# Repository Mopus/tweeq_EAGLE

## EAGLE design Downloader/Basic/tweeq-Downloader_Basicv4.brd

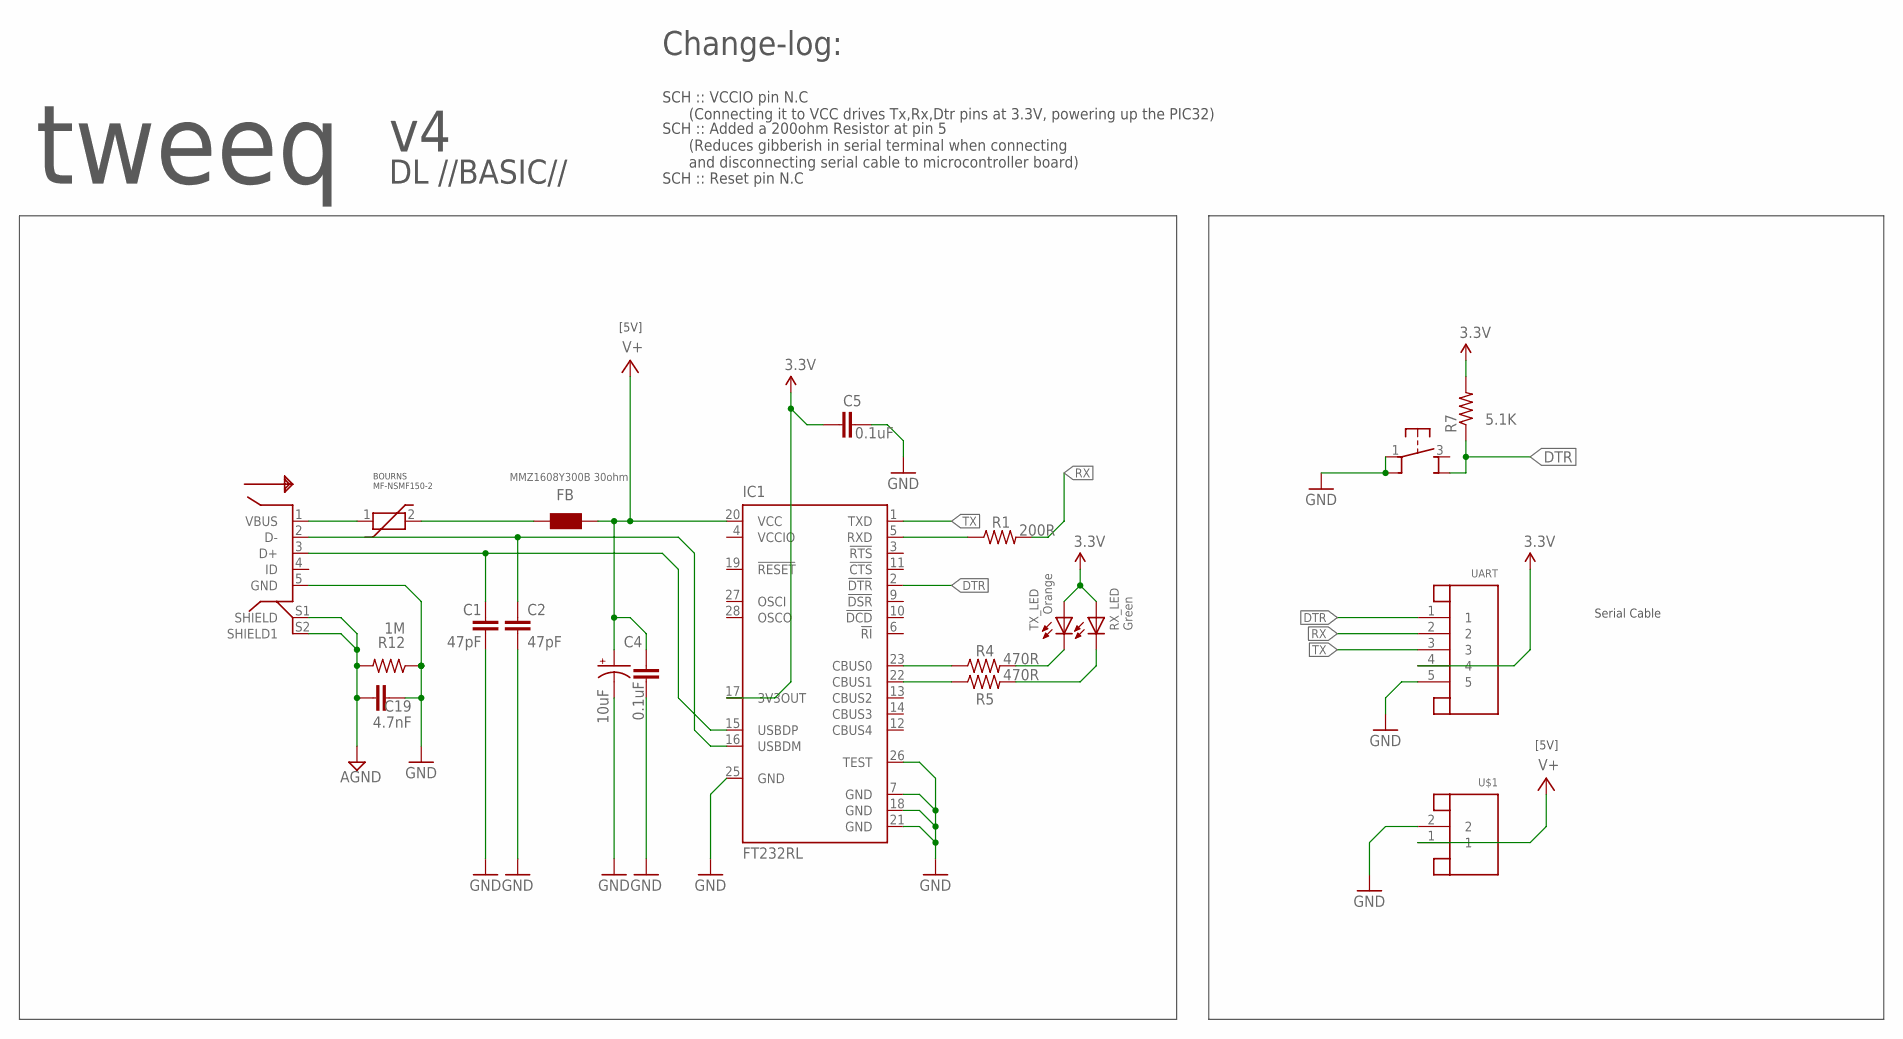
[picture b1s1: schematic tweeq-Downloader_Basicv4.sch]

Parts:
C1, C2: 47pF; C0603K
C3: 10uF; SMC_A
C4, C5: 0.1uF; C0603K
C19: 4.7nF; C0603K
FB: MMZ1608Y300B 30ohm; 0603
IC1: FT232RL; SSOP28
PTC_FUSE: PTC_FUSE/MF-NSMF150-2; 1206F
R1: 200R; R0603
R4, R5: 470R; R0603
R7: 5.1K; R0603
R12: 1M; R0603
RX_LED: Green; CHIP-LED0805
TX_LED: Orange; CHIP-LED0805
U$1: JST-2PINSH; SH1.0-2PIN
U$2: USB/MICRO-5PF-B; MICRO_USB_5PF_B
U$4: PB_MICRO_SMT; PB_SMT_3.5X3X2
UART: JST-5PINSH; SH1.0-5PIN

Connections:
3.3V: C5.1, IC1.17 (3V3OUT), R7.2, RX_LED.A, TX_LED.A, UART.4
AGND: C19.2, R12.2, U$2.S1 (SHIELD), U$2.S2 (SHIELD1)
D+: C1.1, IC1.15 (USBDP), U$2.3 (D+)
D-: C2.1, IC1.16 (USBDM), U$2.2 (D-)
DTR: IC1.2 (!DTR), R7.1, U$4.4 (2A), UART.1
GND: C1.2, C2.2, C3.-, C4.2, C5.2, C19.1, IC1.7 (GND), IC1.18 (GND), IC1.21 (GND), IC1.25 (GND), IC1.26 (TEST), R12.1, U$1.2, U$2.5 (GND), U$4.1, U$4.2 (1A), UART.5
unnamed: PTC_FUSE.1, U$2.1 (VBUS)
unnamed: FB.2, PTC_FUSE.2
unnamed: IC1.5 (RXD), R1.1
unnamed: IC1.23 (CBUS0), R4.1
unnamed: IC1.22 (CBUS1), R5.1
unnamed: R4.2, TX_LED.C
unnamed: R5.2, RX_LED.C
RX: R1.2, UART.2
TX: IC1.1 (TXD), UART.3
V+: C3.+, C4.1, FB.1, IC1.20 (VCC), U$1.1
VCCIO: IC1.4 (VCCIO)

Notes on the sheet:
[5V]
Serial Cable
tweeq
DL //BASIC//
Change-log:
SCH :: VCCIO pin N.C (Connecting it to VCC drives Tx,Rx,Dtr pins at 3.3V, powering up the PIC32)
SCH :: Added a 200ohm Resistor at pin 5 (Reduces gibberish in serial terminal when connecting and disconnecting serial cable to microcontroller board)
SCH :: Reset pin N.C
BOURNS MF-NSMF150-2

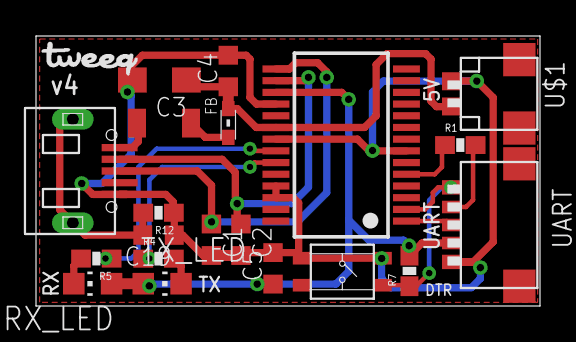
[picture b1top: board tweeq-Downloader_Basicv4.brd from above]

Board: 2 copper layers, 28.0 x 15.0 mm, 22 parts (1 on the bottom side), 16 nets.

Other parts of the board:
U$3: TWEEQ-LOGO-S
U$5: TWEEQ-LOGO-L

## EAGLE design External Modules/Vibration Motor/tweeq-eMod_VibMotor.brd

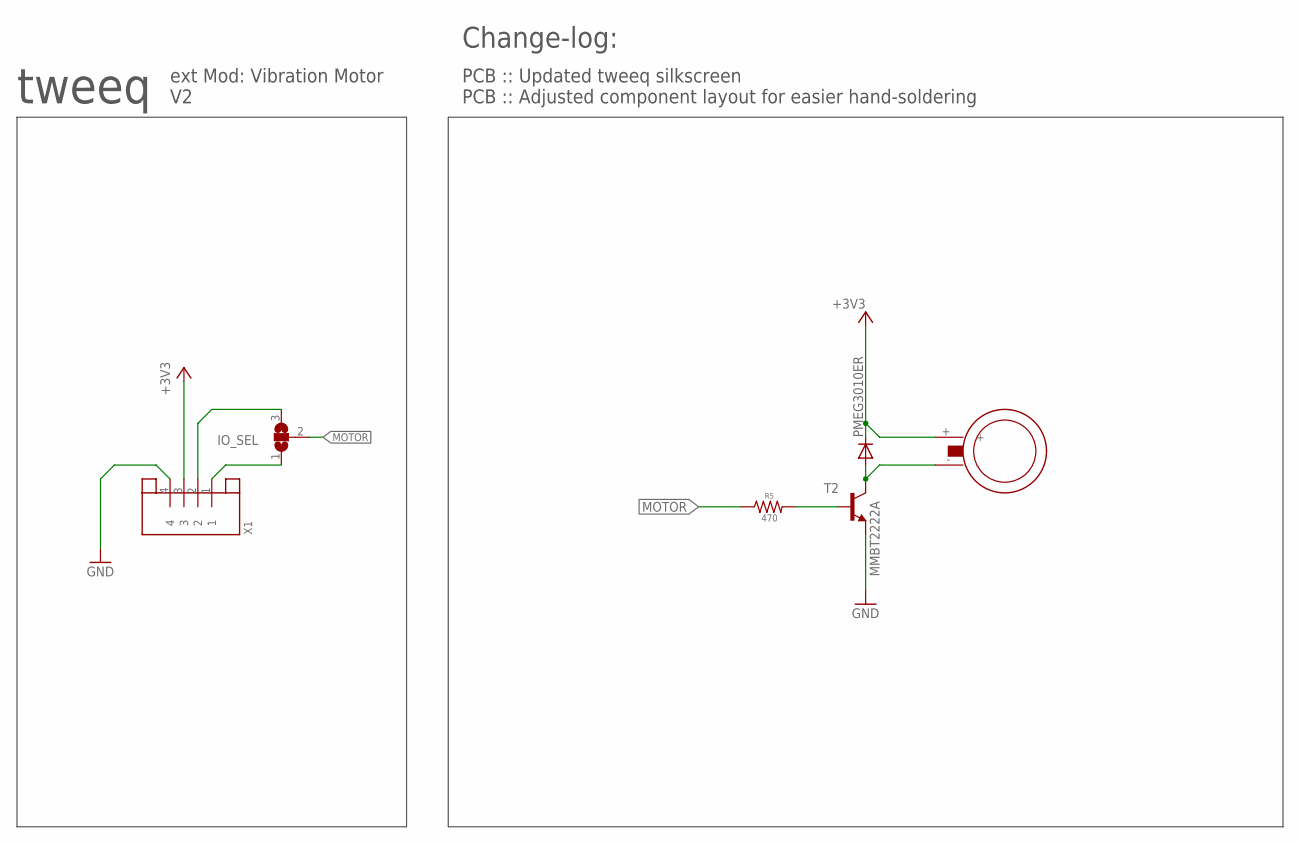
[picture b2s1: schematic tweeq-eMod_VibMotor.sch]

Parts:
IO_SEL: JUMPER_SJ2WS; JUMPER_SJ_S
PMEG3010ER: PMEG3010ER/MOD; SOD123-MOD
R5: 470; R0603
T2: 2N3904MMBT3904; SOT23-3
U$2: VMOTOR_10
X1: JST-4PINSH; SH1.0-4PIN

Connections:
+3V3: PMEG3010ER.C, U$2.+, X1.3
GND: T2.2 (E), X1.4
MOTOR: IO_SEL.2, R5.1
unnamed: R5.2, T2.1 (B)
unnamed: PMEG3010ER.A, T2.3 (C), U$2.-
unnamed: IO_SEL.3, X1.2
unnamed: IO_SEL.1, X1.1

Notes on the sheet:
tweeq
ext Mod: Vibration Motor V2
MMBT2222A
Change-log:
PCB :: Updated tweeq silkscreen PCB :: Adjusted component layout for easier hand-soldering

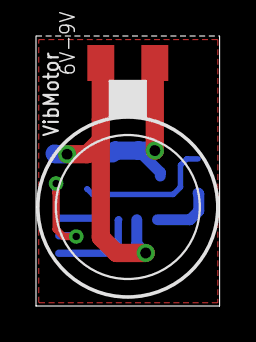
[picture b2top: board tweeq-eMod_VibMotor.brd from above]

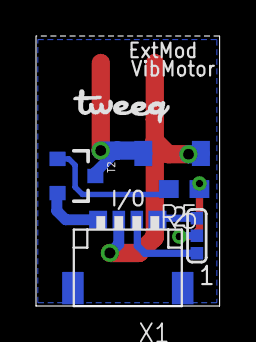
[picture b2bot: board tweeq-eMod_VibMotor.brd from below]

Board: 2 copper layers, 10.2 x 15.0 mm, 7 parts (6 on the bottom side), 7 nets.

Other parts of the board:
U$1: TWEEQ-LOGO-S

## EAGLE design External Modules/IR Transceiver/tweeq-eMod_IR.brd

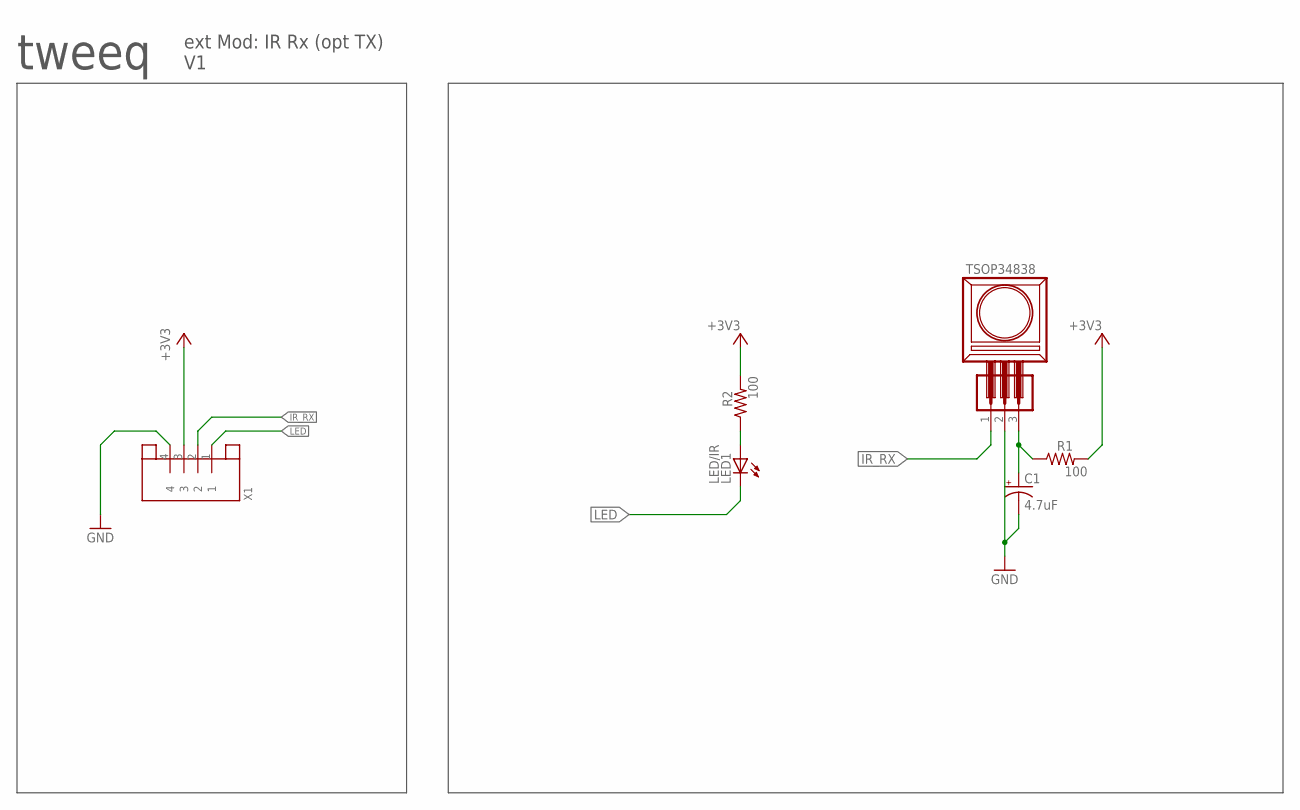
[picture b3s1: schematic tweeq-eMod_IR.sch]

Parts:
C1: 4.7uF; SMC_A
LED1: LED/IR; CHIPLED_0805
R1, R2: 100; R0603
TSOP34838: M03NS-SQ; 1X03-NS-SQ
X1: JST-4PINSH; SH1.0-4PIN

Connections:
+3V3: R1.2, R2.2, X1.3
GND: C1.-, TSOP34838.2, X1.4
IR_RX: TSOP34838.1, X1.2
LED: LED1.C, X1.1
unnamed: LED1.A, R2.1
unnamed: C1.+, R1.1, TSOP34838.3

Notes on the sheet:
tweeq
ext Mod: IR Rx (opt TX) V1

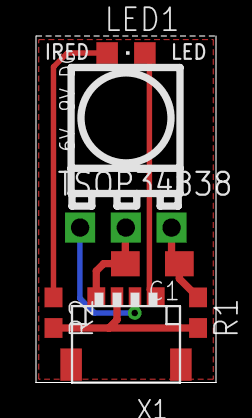
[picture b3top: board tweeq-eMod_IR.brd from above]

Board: 2 copper layers, 10.0 x 19.2 mm, 7 parts (1 on the bottom side), 6 nets.

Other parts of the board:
U$3: TWEEQ-LOGO-M

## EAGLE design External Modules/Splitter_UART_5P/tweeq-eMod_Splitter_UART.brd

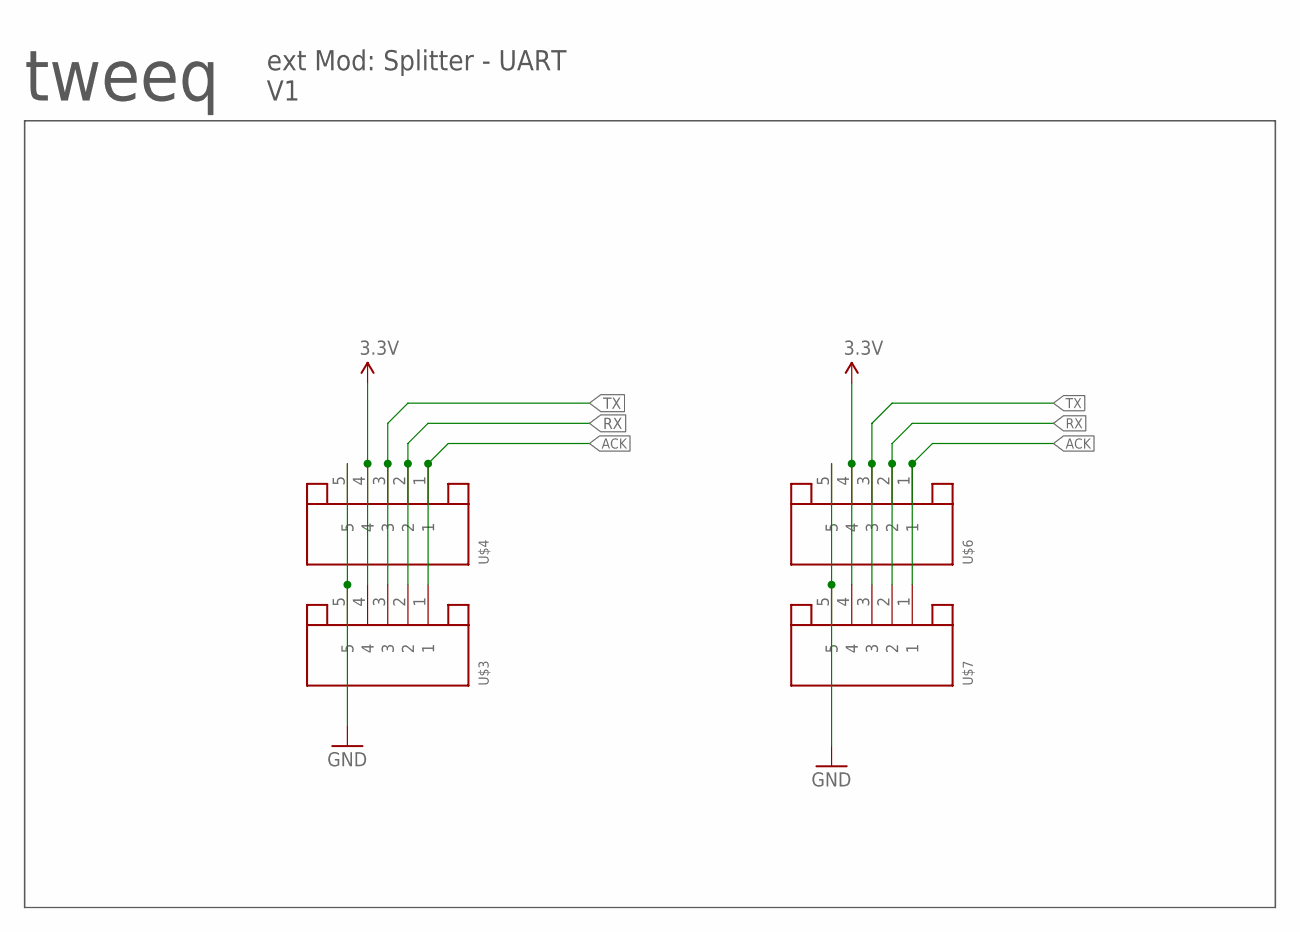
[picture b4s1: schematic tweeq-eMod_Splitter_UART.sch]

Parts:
U$3, U$4, U$6, U$7: JST-5PINSH; SH1.0-5PIN

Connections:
3.3V: U$3.4, U$4.4, U$6.4, U$7.4
ACK: U$3.1, U$4.1, U$6.1, U$7.1
GND: U$3.5, U$4.5, U$6.5, U$7.5
RX: U$3.2, U$4.2, U$6.2, U$7.2
TX: U$3.3, U$4.3, U$6.3, U$7.3

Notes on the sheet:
tweeq
ext Mod: Splitter - UART V1

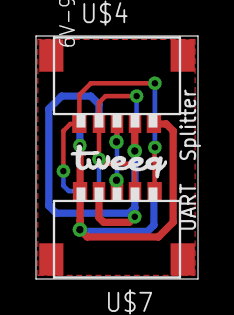
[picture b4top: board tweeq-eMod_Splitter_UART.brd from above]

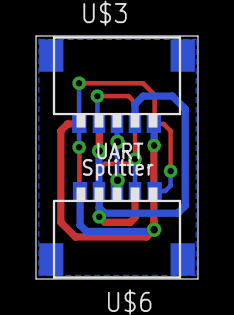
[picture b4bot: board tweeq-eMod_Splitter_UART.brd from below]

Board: 2 copper layers, 9.0 x 13.5 mm, 5 parts (2 on the bottom side), 5 nets.

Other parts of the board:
U$1: TWEEQ-LOGO-S

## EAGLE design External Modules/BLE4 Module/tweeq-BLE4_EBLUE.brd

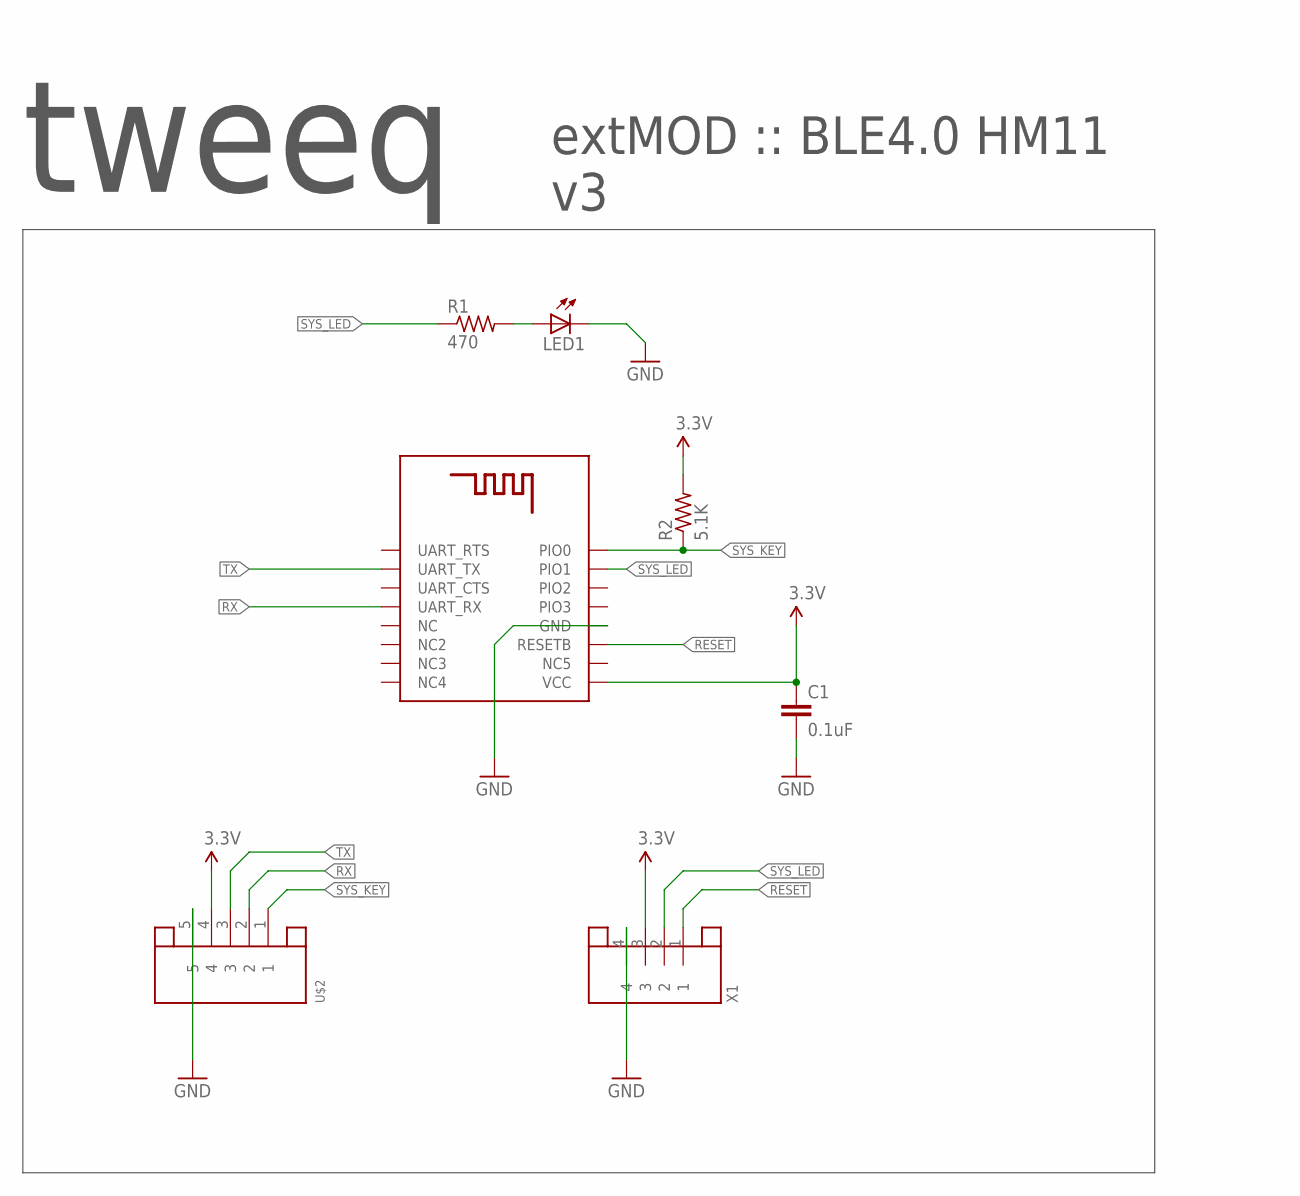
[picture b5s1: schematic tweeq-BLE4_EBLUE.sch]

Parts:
C1: 0.1uF; C0603K
LED1: LEDCHIP-LED0805; CHIP-LED0805
R1: 470; R0603
R2: 5.1K; R0603
U$1: EBLUE_BLE4.0_HM11HM11; BLE4.0_HM11
U$2: JST-5PINEDGE; SH1.0-5PIN/BLE_EDGE
X1: JST-4PINSH-EDGE; SH1.0-4PIN/BLE_EDGE

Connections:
3.3V: C1.1, R2.2, U$1.P$9 (VCC), U$2.4, X1.3
GND: C1.2, LED1.C, U$1.P$12 (GND), U$2.5, X1.4
unnamed: LED1.A, R1.2
RESET: U$1.P$11 (RESETB), X1.1
RX: U$1.P$4 (UART_RX), U$2.2
SYS_KEY: R2.1, U$1.P$16 (PIO0), U$2.1
SYS_LED: R1.1, U$1.P$15 (PIO1), X1.2
TX: U$1.P$2 (UART_TX), U$2.3

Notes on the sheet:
tweeq
extMOD :: BLE4.0 HM11 v3

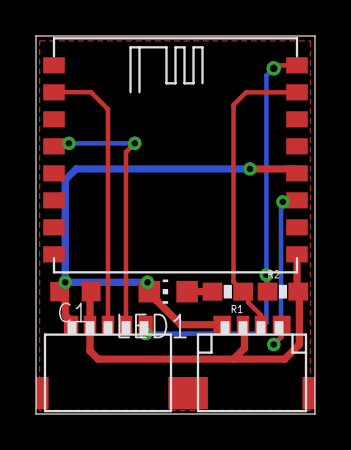
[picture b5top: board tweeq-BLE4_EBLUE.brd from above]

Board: 2 copper layers, 15.5 x 21.0 mm, 9 parts (2 on the bottom side), 8 nets.

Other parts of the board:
U$3: LOGO_BLUETOOTH
U$4: TWEEQ-LOGO-M

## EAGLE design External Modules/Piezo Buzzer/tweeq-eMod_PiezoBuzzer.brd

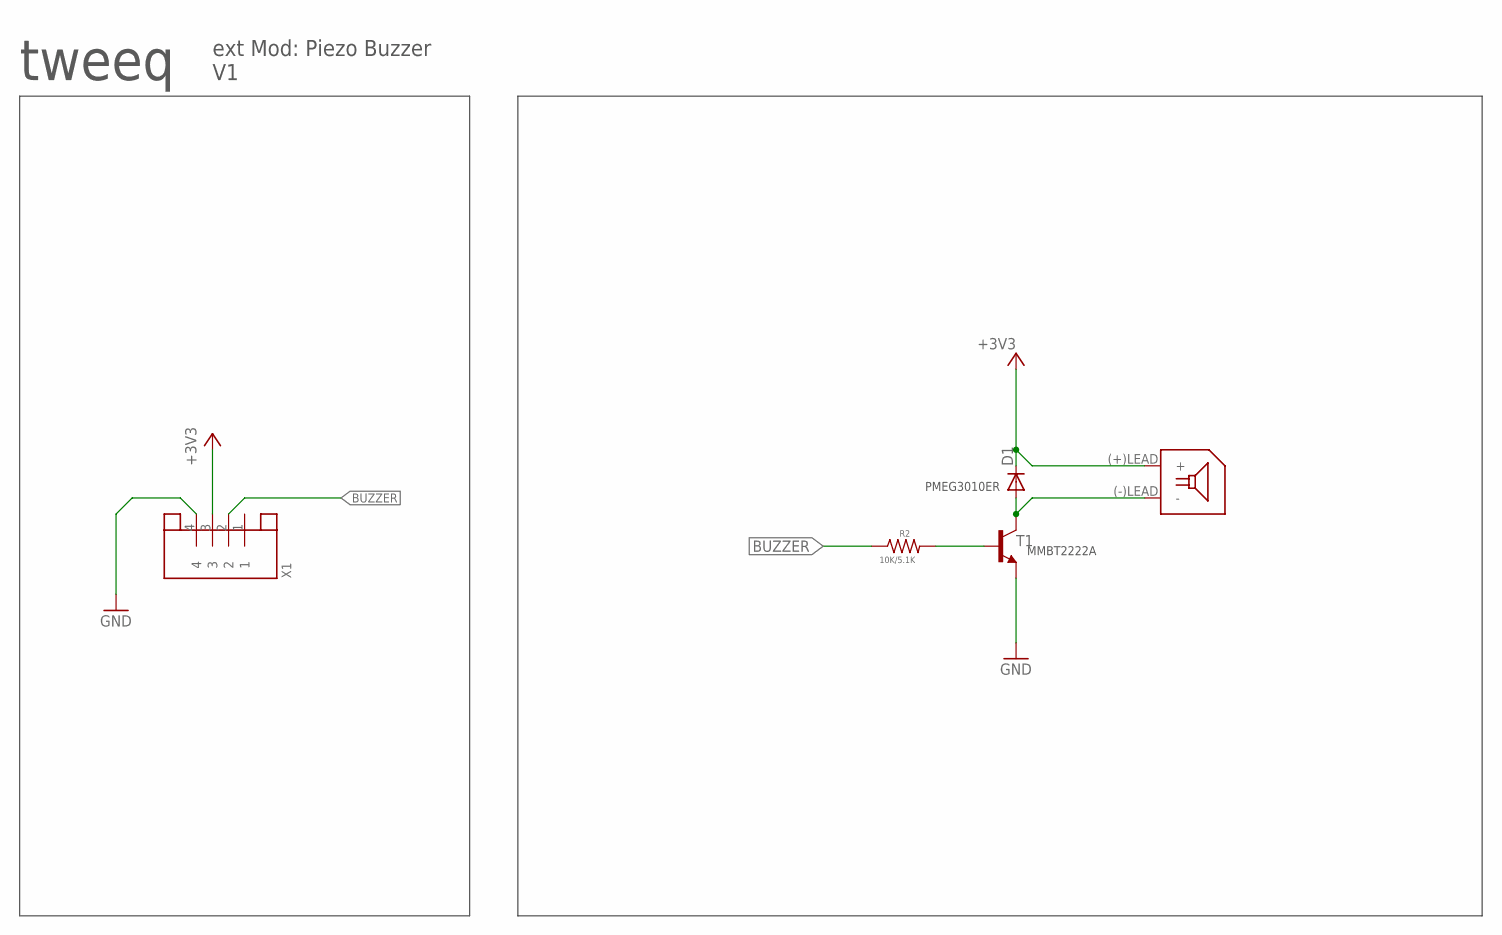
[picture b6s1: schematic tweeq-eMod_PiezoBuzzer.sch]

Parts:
D1: PMEG3010ER; SOD123-MOD
R2: 10K/5.1K; R0402
T1: 2N3904MMBT3904; SOT23-3
U$5: SMD_PEIZO_BUZZER-DET; DET801J-13-G
X1: JST-4PINSH; SH1.0-4PIN

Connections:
+3V3: D1.C, U$5.(+)LEAD (+), X1.3
BUZZER: R2.1, X1.2
GND: T1.2 (E), X1.4
unnamed: R2.2, T1.1 (B)
unnamed: D1.A, T1.3 (C), U$5.(-)LEAD (-)

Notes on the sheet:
tweeq
ext Mod: Piezo Buzzer V1
PMEG3010ER
MMBT2222A

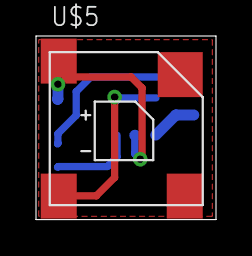
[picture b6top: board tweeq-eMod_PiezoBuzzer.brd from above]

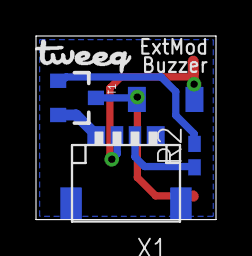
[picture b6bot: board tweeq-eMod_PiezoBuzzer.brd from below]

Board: 2 copper layers, 10.0 x 10.2 mm, 6 parts (5 on the bottom side), 5 nets.

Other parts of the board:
U$1: TWEEQ-LOGO-S

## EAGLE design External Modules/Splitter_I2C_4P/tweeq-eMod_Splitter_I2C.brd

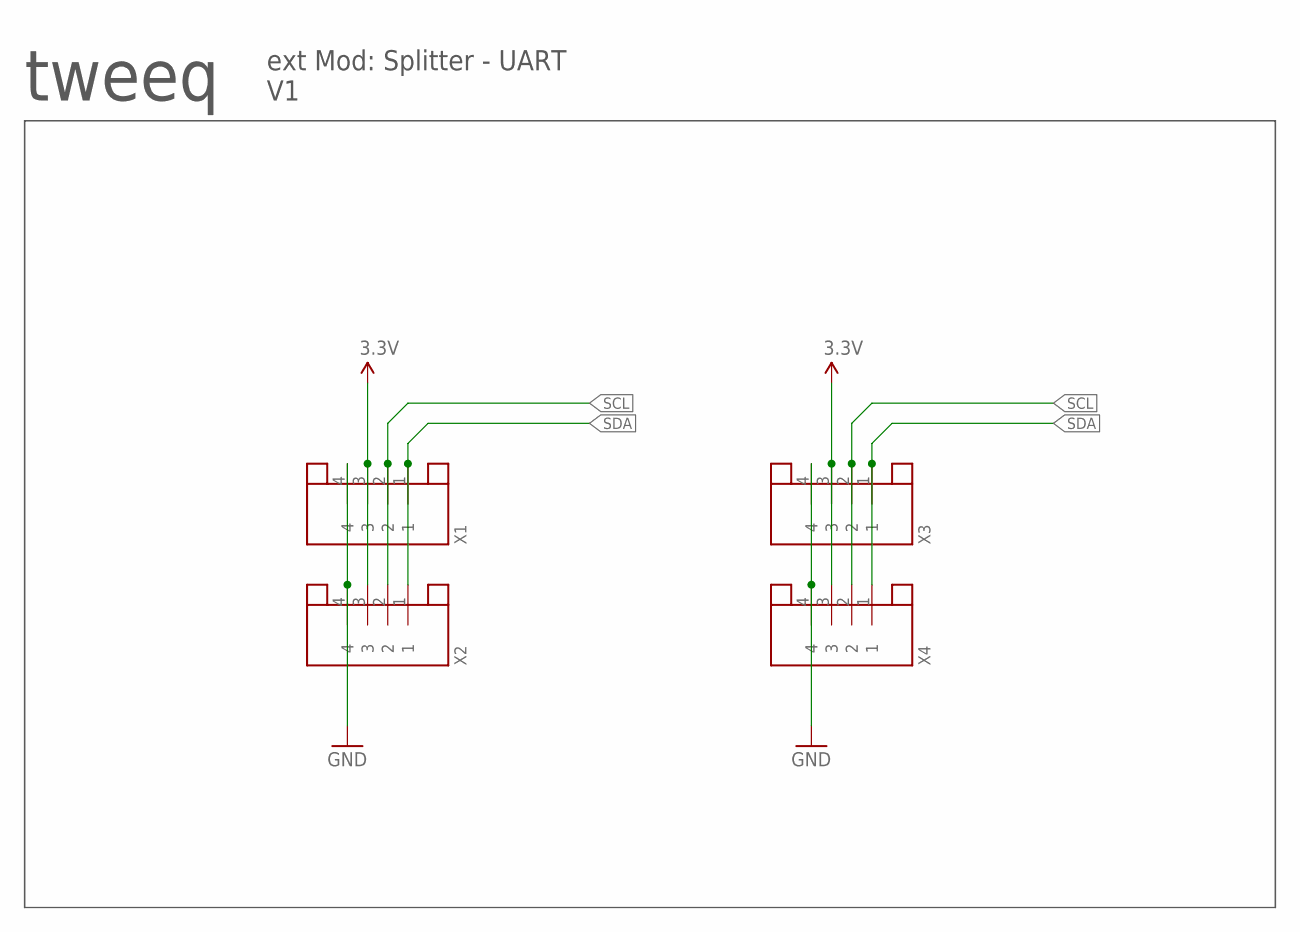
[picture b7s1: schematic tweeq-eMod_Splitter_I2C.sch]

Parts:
X1, X2, X3, X4: JST-4PINSH; SH1.0-4PIN

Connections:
3.3V: X1.3, X2.3, X3.3, X4.3
GND: X1.4, X2.4, X3.4, X4.4
SCL: X1.2, X2.2, X3.2, X4.2
SDA: X1.1, X2.1, X3.1, X4.1

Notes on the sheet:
tweeq
ext Mod: Splitter - UART V1

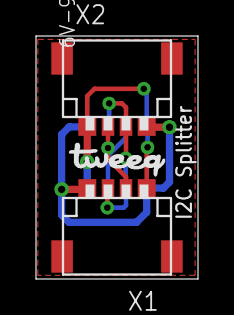
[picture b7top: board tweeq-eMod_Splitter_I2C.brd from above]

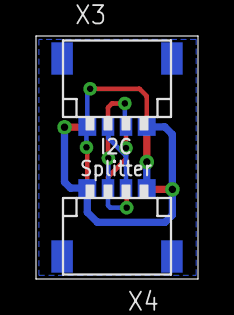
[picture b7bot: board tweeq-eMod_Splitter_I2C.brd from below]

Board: 2 copper layers, 9.0 x 13.5 mm, 5 parts (2 on the bottom side), 4 nets.

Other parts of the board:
U$1: TWEEQ-LOGO-S

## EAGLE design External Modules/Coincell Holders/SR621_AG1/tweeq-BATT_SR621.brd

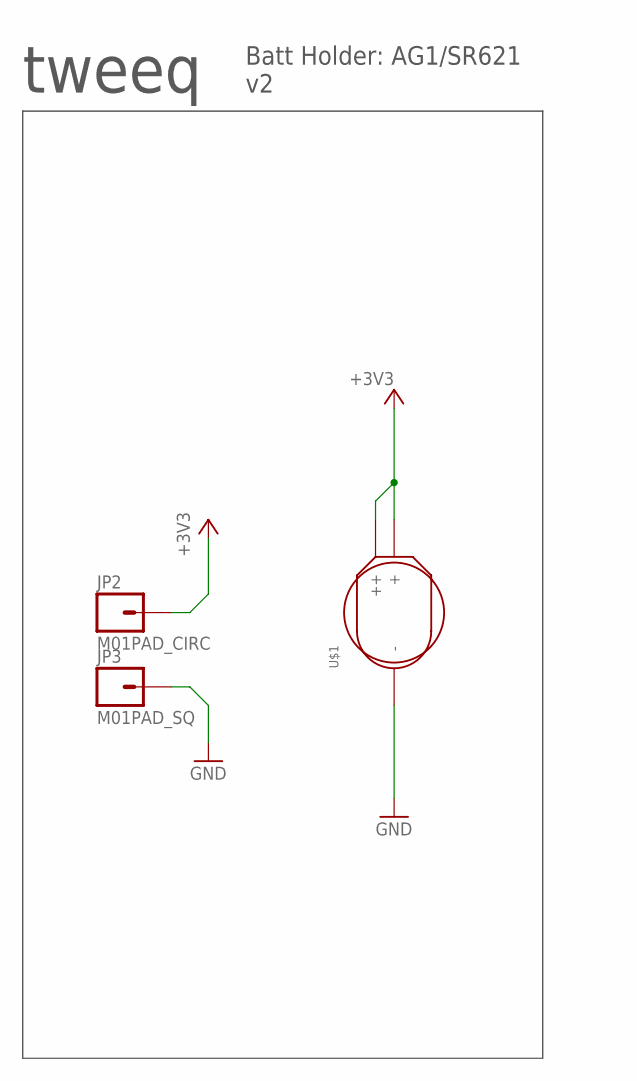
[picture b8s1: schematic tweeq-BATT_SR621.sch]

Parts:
JP2: M01PAD_CIRC; 1X01_PAD_CIRC
JP3: M01PAD_SQ; 1X01_PAD_SQ
U$1: BATT_COMMON/AG1; BATT_AG1_TH

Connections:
+3V3: JP2.1, U$1.+1 (+), U$1.+2 (++)
GND: JP3.1, U$1.-

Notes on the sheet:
tweeq
Batt Holder: AG1/SR621 v2

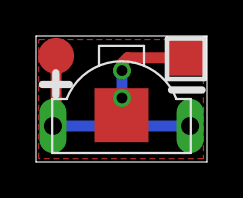
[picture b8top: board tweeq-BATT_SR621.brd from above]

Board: 2 copper layers, 9.5 x 7.0 mm, 4 parts (1 on the bottom side), 2 nets.

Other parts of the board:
U$2: TWEEQ-LOGO-S

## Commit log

2015-05-14 Release of EAGLE files for tweeq cores
2015-05-21 Release of EAGLE Files for FB & IB Boards
2015-05-21 Release of EAGLE for Stamp Modules
2015-05-21 External Plug & Play modules for tweeq
2015-05-21 tweeq Downloader Board
    with DTR enabled button for bootloader mode (avrdude)
